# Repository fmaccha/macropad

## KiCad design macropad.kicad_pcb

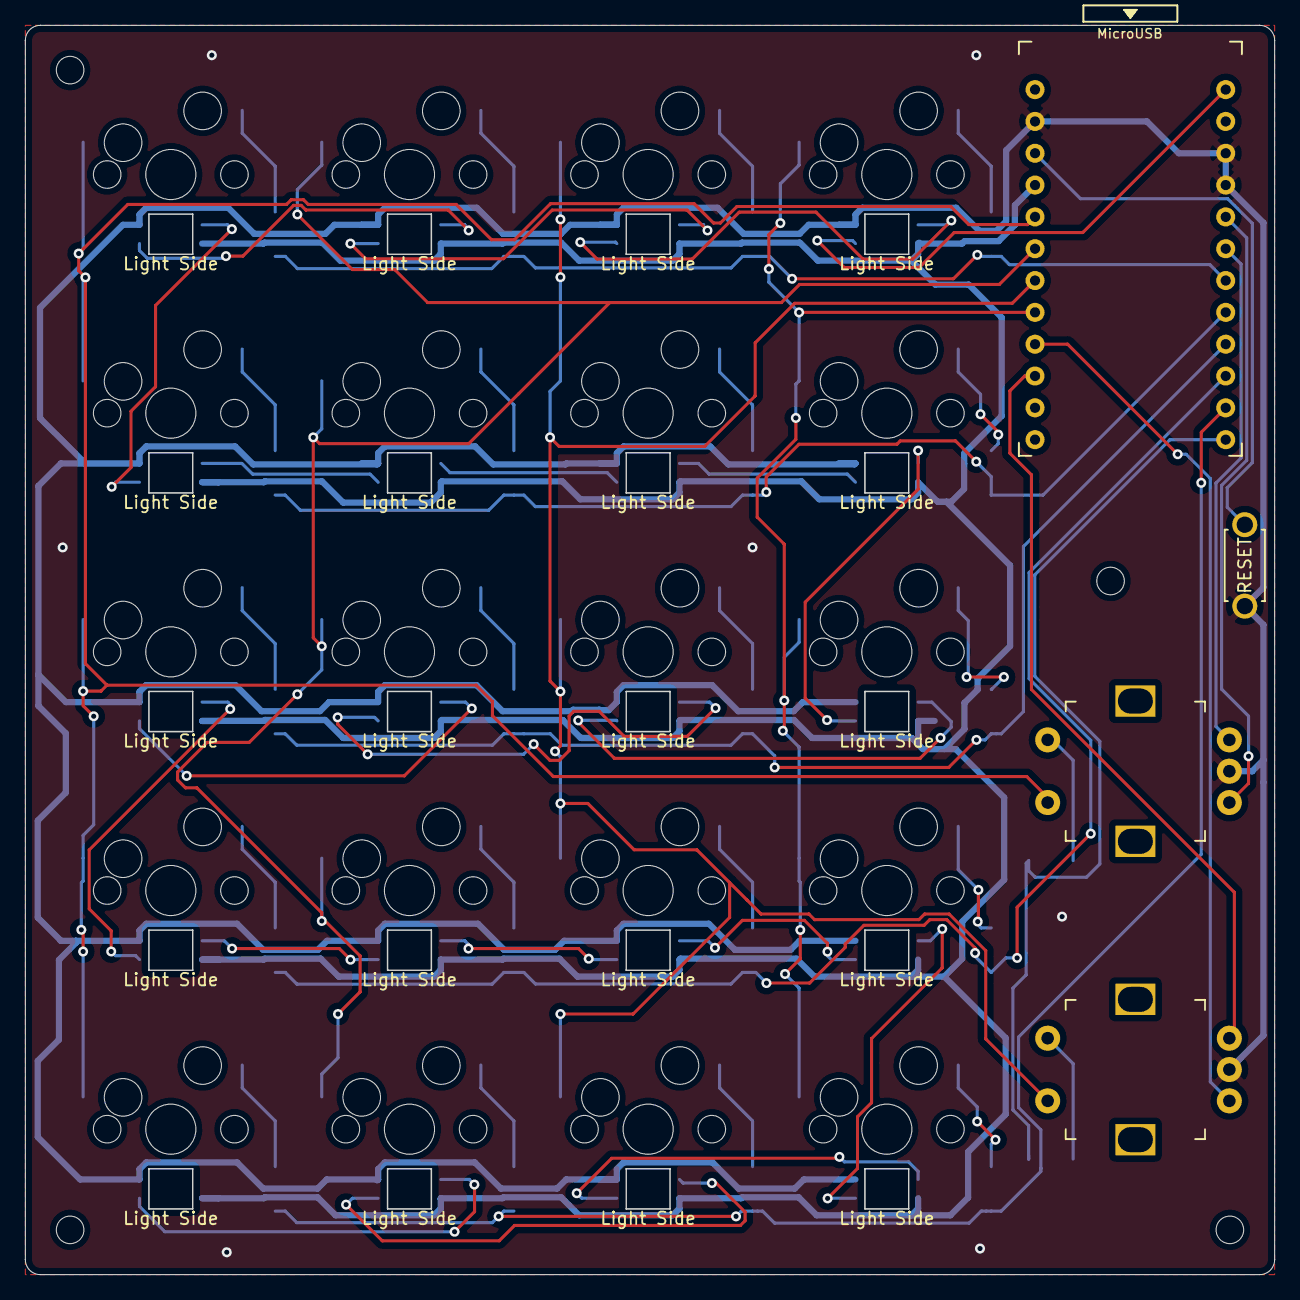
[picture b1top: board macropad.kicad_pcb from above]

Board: 2 copper layers, 99.7 x 99.7 mm, 70 parts (0 on the bottom side), 59 nets.

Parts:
D1, D2, D3, D4, D5, D6, D7, D8, D9, D10, D11, D12, D13, D14, D15, D16, D17, D18, D19, D20, D21, D22: D; Diode_SMD
L1, L2, L3, L4, L5, L6, L7, L8, L9, L10, L11, L12, L13, L14, L15, L16, L17, L18, L19, L20: SK6812MINI; LED_SK6812MINI-E_BL
Ref**: Val**; m2_Screw_Hole
Ref**#2, Ref**#3, Ref**#4: Val**; m2_Screw_Hole
SW1, SW2, SW3, SW4, SW5, SW6, SW7, SW8, SW9, SW10, SW11, SW12, SW13, SW14, SW15, SW16, SW17, SW18, SW19, SW20: SW_PUSH; CherryMX_Hotswap_1.0u
SW21, SW22: Rotary_Encoder_Switch; RotaryEncoder_EC12E
SW23: RESET_SWITCH; ResetSW_1side
U1: ProMicro; ProMicro_v3.5

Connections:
GND: L1.2, L2.2, L3.2, L4.2, L5.2, L6.2, L7.2, L8.2, L9.2, L10.2, L11.2, L12.2, L13.2, L14.2, L15.2, L16.2, L17.2, L18.2, L19.2, L20.2, SW21.C, SW22.C, SW23.2, U1.3, U1.4, U1.23
unnamed: D1.2, SW1.2
unnamed: D2.2, SW2.2
unnamed: D3.2, SW3.2
unnamed: D4.2, SW4.2
unnamed: D5.2, SW5.2
unnamed: D6.2, SW6.2
unnamed: D7.2, SW7.2
unnamed: D8.2, SW8.2
unnamed: D9.2, SW9.2
unnamed: D10.2, SW10.2
unnamed: D11.2, SW11.2
unnamed: D12.2, SW12.2
unnamed: D13.2, SW13.2
unnamed: D14.2, SW14.2
unnamed: D15.2, SW15.2
unnamed: D16.2, SW16.2
unnamed: D17.2, SW17.2
unnamed: D18.2, SW18.2
unnamed: D19.2, SW19.2
unnamed: D20.2, SW20.2
unnamed: D21.2, SW21.S1
unnamed: D22.2, SW22.S1
unnamed: L1.1, L5.3
unnamed: L1.3, L2.1
unnamed: L2.3, L3.1
unnamed: L3.3, L4.1
unnamed: L5.1, L6.3
unnamed: L6.1, L7.3
unnamed: L7.1, L8.3
unnamed: L9.3, L10.1
unnamed: L10.3, L11.1
unnamed: L11.3, L12.1
unnamed: L8.1, L12.3
unnamed: L13.1, L14.3
unnamed: L9.1, L13.3
unnamed: L14.1, L15.3
unnamed: L15.1, L16.3
unnamed: L16.1, L20.3
unnamed: L17.3, L18.1
unnamed: L18.3, L19.1
unnamed: L19.3, L20.1
VCC: L1.4, L2.4, L3.4, L4.4, L5.4, L6.4, L7.4, L8.4, L9.4, L10.4, L11.4, L12.4, L13.4, L14.4, L15.4, L16.4, L17.4, L18.4, L19.4, L20.4, U1.21
col0: SW1.1, SW5.1, SW9.1, SW13.1, SW17.1, SW21.S2, U1.20
col1: SW2.1, SW6.1, SW10.1, SW14.1, SW18.1, U1.19
col2: SW3.1, SW7.1, SW11.1, SW15.1, SW19.1, SW22.S2, U1.18
col3: SW4.1, SW8.1, SW12.1, SW16.1, SW20.1, U1.17
led: L4.3, U1.1
reset: SW23.1, U1.22
rotaryA: SW21.A, U1.5
rotaryB: SW21.B, U1.6
rotaryC: SW22.A, U1.16
rotaryD: SW22.B, U1.15
row0: D1.1, D2.1, D3.1, D4.1, U1.7
row1: D5.1, D6.1, D7.1, D8.1, U1.8
row2: D9.1, D10.1, D11.1, D12.1, U1.9
row3: D13.1, D14.1, D15.1, D16.1, U1.10
row4: D17.1, D18.1, D19.1, D20.1, U1.11
row5: D21.1, D22.1, U1.12

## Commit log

2021-10-31 add footprint placement and a bit of routing
2021-11-21 rev1
